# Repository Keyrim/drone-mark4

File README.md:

# drone-mark4 - "throw-drone"

A 5-inch racing drone is thrown by hand, motors off. The firmware detects the
throw, predicts the apex of the parabola, spins the motors up ahead of time,
recovers from an arbitrary attitude (the drone may tumble) and settles into a
stable hover. Everything is rewritten from scratch - firmware, simulator,
tooling - as a deliberate learning project. Behavioral reference: ArduPilot's
"Throw Mode".

Documentation:

- [API reference](https://keyrim.github.io/drone-mark4/) - Doxygen over the C++ of every node plus these pages, published from `main`
- [docs/architecture.md](docs/architecture.md) - system architecture (diagrams)
- [docs/plan-dev.md](docs/plan-dev.md) - development plan and reference document
- [docs/contributing/cpp-guidelines.md](docs/contributing/cpp-guidelines.md) - C++ coding guidelines
- [docs/mobile-app.md](docs/mobile-app.md) - phone as gateway: what the two mobile PoCs established, and the roadmap of `software/mobile`
- [docs/comm-design.md](docs/comm-design.md) - communication stack: transport presence, messaging postman, pull discovery, and the services on the messenger (issues #29 and #31)
- [worktrees/README.md](worktrees/README.md) - git worktrees: where they live, how to bring one up, build it, open it, remove it

## Modules

- `flight-core/` - pure flight core: no dynamic allocation, no
  exceptions/RTTI, no clock access. `float` everywhere
  (`-Wdouble-promotion` as an error).
- `platform/` - 3 abstract services (AbsSensorSource, AbsMotorSink,
  AbsClock) plus one implementation set per variant; commands come in
  through the `messaging` component, not through a platform service. No singletons: each executable has an
  explicit composition root in its main.
- `protocol/` - one protobuf schema (`mark4.proto`), codecs generated at
  build time for C/C++ (nanopb) and GDScript (godobuf); spoken by
  everyone (firmware, sim, Godot, hub).
- `telemetry/` - the registry of named measures a node exposes, declared
  next to the variables they read. A leaf: names, units and pointers, no
  wire. A ground tool discovers the list and streams the subset it wants.
- `transport/` - the interface manager: frames every payload with a source
  and a destination node, learns every node it hears, relays between links.
- `log/` - one logging module per source file, filterable at runtime, its
  lines going out on the wire like everything else.

## Build

### Inside the devcontainer (recommended)

Open `drone-mark4.code-workspace` in VS Code -> "Reopen in Container". The
workspace exposes the repo root and `software/` (the CMake project root) as
folders and carries the debug configurations. Both toolchains (native gcc +
arm-none-eabi) and the pinned tooling live in the image.

```sh
# Desktop: build + tests
cmake --preset desktop && cmake --build --preset desktop && ctest --preset desktop

# Sanitizers (ASan/UBSan)
cmake --preset desktop-san && cmake --build --preset desktop-san && ctest --preset desktop-san

# STM32F405 cross-compilation (Cortex-M4F) -> firmware.elf
cmake --preset stm32 && cmake --build --preset stm32

# Sign of life (runs its loop with or without a plant, no frame limit by default)
./software/build/desktop/drone_sim/drone_sim
```

### Mobile app (Flutter, Android)

`software/mobile/` is the Flutter project; the image carries Flutter, the
Android SDK, the NDK and adb. The phone is reached over Wi-Fi (developer
options -> wireless debugging), the container being on the host network:

```sh
./scripts/adb_wifi.sh                     # discovers the phone over mDNS, pairs once, connects
cd software/mobile && flutter pub get && ./tool/gen.sh   # generated codec, wire hash
flutter run                               # or: flutter build apk --debug --target-platform android-arm64
```

### Manual build (outside the container)

Prerequisites: CMake >= 3.25, Ninja, gcc, arm-none-eabi-gcc (ARM tarball
14.2.rel1), clang-format/clang-tidy 21 for the checks. Same commands as above.

### Code quality

```sh
git ls-files '*.cpp' '*.hpp' '*.c' '*.h' | xargs clang-format --dry-run --Werror
run-clang-tidy -p software/build/desktop "$(pwd)/(apps|flight-core|platform|protocol|tests)/"
```

## Simulation chain

Three processes are transport nodes on udp/47820 and find each other by
the transport's keepalives; the plant and the hub then ask every node that
appears who it is. The Godot plant spawns one virtual drone per node that
answers `drone_sim` and feeds it sensor frames in lockstep, `drone_sim` answers with
actuator frames and streams its status, logs and telemetry to the nodes
that subscribed, the hub decodes it for the pages. Nothing is configured,
start them in any order.

```sh
# Terminal 1 - flight process (one per virtual drone wanted)
./software/build/desktop/drone_sim/drone_sim

# Terminal 2 - the plant (the desktop build generated its codec)
godot --path sim-godot

# Terminal 3 - decoding endpoint and web pages on http://127.0.0.1:47810
./software/build/desktop/hub/hub
```

Every python tool in the repository runs on the standard library alone, so
there is nothing to install first.

## Debugging from VS Code

`drone-mark4.code-workspace` provides:

- `drone_sim (gdb)` - debugs the CMake launch target: pick the `desktop`
  preset and the `drone_sim` target in the CMake Tools status bar, the
  target is rebuilt automatically before each launch;
- `sim_stub (python)` - streams frames until stopped.

The default build task (Ctrl+Shift+B) builds the active CMake configure
preset.

## CI

- `devcontainer-image.yml` - reusable workflow that tags the image by a hash
  of the Dockerfile, builds and pushes it to GHCR
  (`ghcr.io/keyrim/drone-mark4-devcontainer`, public) only when that tag is
  missing, and retags `:latest` on main.
- `ci.yml` and `docs.yml` each call it as a first `image` job and run every
  other job inside the digest it returns, so a Dockerfile change is built and
  tested inside the PR that makes it, with no digest to bump by hand. `ci.yml`
  has 8 parallel jobs: desktop+tests, stm32, esp32, desktop-san, pages,
  mobile (gen, flutter analyze, format, test, debug apk), clang-format+ascii,
  clang-tidy.

## J-Link license note

The development image downloads the J-Link tools from segger.com: the
automated download (`--post-data accept_license_agreement=accepted`) implies
acceptance of the [Segger license](https://www.segger.com/downloads/jlink).
If that is a problem, comment out the J-Link layer in the `Dockerfile` or
install the .deb manually. The whole J-Link stack (`JLinkExe`,
`JLinkGDBServer`, `JLinkRTTClient`) runs inside the container: the probe is
attached to WSL with `usbipd` and reaches the container through the `/dev`
bind mount (see `docs/bring-up.md`).

## License

[MIT](LICENSE).

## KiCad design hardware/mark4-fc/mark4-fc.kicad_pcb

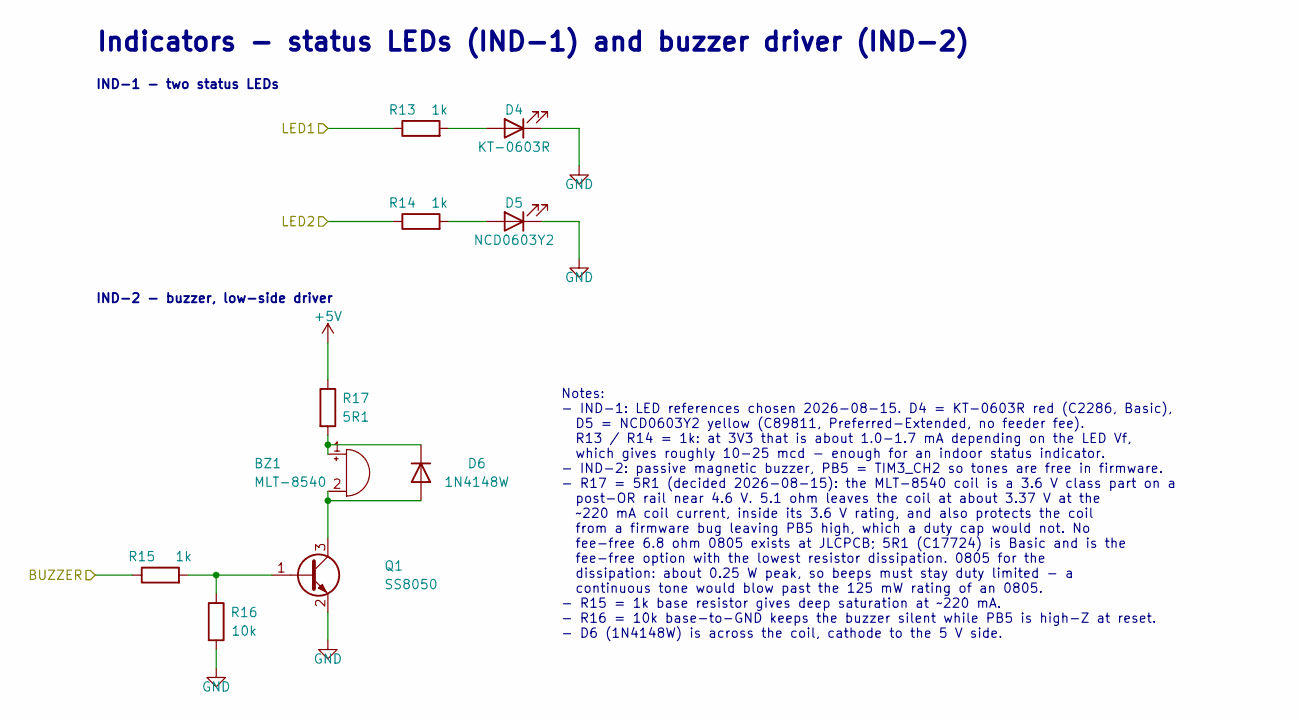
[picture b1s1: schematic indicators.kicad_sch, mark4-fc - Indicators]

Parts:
BZ1: MLT-8540; Buzzer_MLT-8540; MPN MLT-8540; LCSC C95300
D4: KT-0603R; LED_0603_1608Metric; MPN KT-0603R; LCSC C2286
D5: NCD0603Y2; LED_0603_1608Metric; MPN NCD0603Y2; LCSC C89811
D6: 1N4148W; D_SOD-123; MPN 1N4148W; LCSC C81598
Q1: SS8050; SOT-23; MPN S8050; LCSC C2146
R13, R14, R15: 1k; R_0603_1608Metric; MPN 0603WAF1001T5E; LCSC C21190
R16: 10k; R_0603_1608Metric; MPN 0603WAF1002T5E; LCSC C25804
R17: 5R1; R_0805_2012Metric; MPN 0805W8F510KT5E; LCSC C17724

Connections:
+5V: R17.1; also elsewhere on the board
/BUZZER: R15.1; also elsewhere on the board
/LED1: R13.1; also elsewhere on the board
/LED2: R14.1; also elsewhere on the board
GND: D4.1 (K), D5.1 (K), Q1.2 (E), R16.2; also elsewhere on the board
unnamed: BZ1.1 (+), D6.1 (K), R17.2
unnamed: BZ1.2 (-), D6.2 (A), Q1.3 (C)
unnamed: D4.2 (A), R13.2
unnamed: D5.2 (A), R14.2
unnamed: Q1.1 (B), R15.2, R16.1

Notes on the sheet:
IND-2 - buzzer, low-side driver
Notes: - IND-1: LED references chosen 2026-08-15. D4 = KT-0603R red (C2286, Basic), D5 = NCD0603Y2 yellow (C89811, Preferred-Extended, no feeder fee). R13 / R14 = 1k: at 3V3 that is about 1.0-1.7 mA depending on the LED Vf, which gives roughly 10-25 mcd - enough for an indoor status indicator. - IN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
Indicators - status LEDs (IND-1) and buzzer driver (IND-2)
IND-1 - two status LEDs

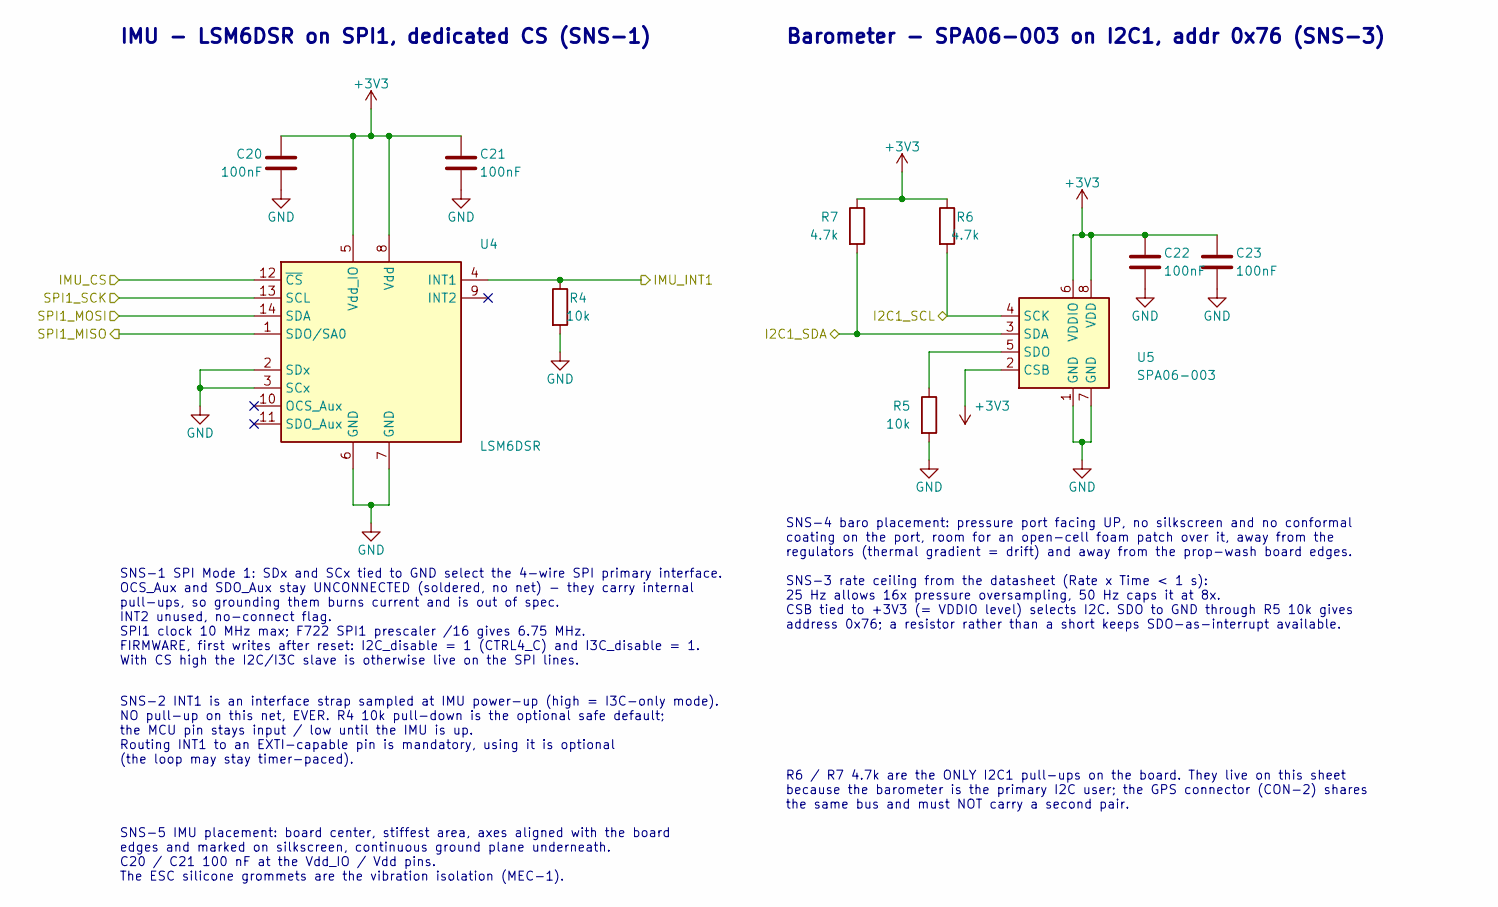
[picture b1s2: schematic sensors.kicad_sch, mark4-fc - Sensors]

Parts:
C20, C21, C22, C23: 100nF; C_0603_1608Metric; MPN CC0603KRX7R9BB104; LCSC C14663
R4, R5: 10k; R_0603_1608Metric; MPN 0603WAF1002T5E; LCSC C25804
R6, R7: 4.7k; R_0603_1608Metric; MPN 0603WAF4701T5E; LCSC C23162
U4: LSM6DSR; LGA-14_3x2.5mm_P0.5mm_LayoutBorder3x4y; MPN LSM6DSRTR; LCSC C784817
U5: SPA06-003; Goertek_LGA-8_2x2.5mm_P0.65mm_ClockwisePinNumbering; MPN SPA06-003; LCSC C30589048

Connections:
+3V3: C20.1, C21.1, C22.1, C23.1, R6.1, R7.1, U4.5 (Vdd_IO), U4.8 (Vdd), U5.2 (CSB), U5.6 (VDDIO), U5.8 (VDD); also elsewhere on the board
/I2C1_SCL: R6.2, U5.4 (SCK); also elsewhere on the board
/I2C1_SDA: R7.2, U5.3 (SDA); also elsewhere on the board
/IMU_CS: U4.12 (~CS); also elsewhere on the board
/IMU_INT1: R4.1, U4.4 (INT1); also elsewhere on the board
/SPI1_MISO: U4.1 (SDO/SA0); also elsewhere on the board
/SPI1_MOSI: U4.14 (SDA); also elsewhere on the board
/SPI1_SCK: U4.13 (SCL); also elsewhere on the board
GND: C20.2, C21.2, C22.2, C23.2, R4.2, R5.2, U4.2 (SDx), U4.3 (SCx), U4.6 (GND), U4.7 (GND), U5.1 (GND), U5.7 (GND); also elsewhere on the board
unnamed: R5.1, U5.5 (SDO)

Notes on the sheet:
SNS-5 IMU placement: board center, stiffest area, axes aligned with the board edges and marked on silkscreen, continuous ground plane underneath. C20 / C21 100 nF at the Vdd_IO / Vdd pins. The ESC silicone grommets are the vibration isolation (MEC-1).
SNS-4 baro placement: pressure port facing UP, no silkscreen and no conformal coating on the port, room for an open-cell foam patch over it, away from the regulators (thermal gradient = drift) and away from the prop-wash board edges. SNS-3 rate ceiling from the datasheet (Rate x Time < 1 s): 25 Hz 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
Barometer - SPA06-003 on I2C1, addr 0x76 (SNS-3)
SNS-1 SPI Mode 1: SDx and SCx tied to GND select the 4-wire SPI primary interface. OCS_Aux and SDO_Aux stay UNCONNECTED (soldered, no net) - they carry internal pull-ups, so grounding them burns current and is out of spec. INT2 unused, no-connect flag. SPI1 clock 10 MHz max; F722 SPI1 prescaler /16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
IMU - LSM6DSR on SPI1, dedicated CS (SNS-1)
SNS-2 INT1 is an interface strap sampled at IMU power-up (high = I3C-only mode). NO pull-up on this net, EVER. R4 10k pull-down is the optional safe default; the MCU pin stays input / low until the IMU is up. Routing INT1 to an EXTI-capable pin is mandatory, using it is optional (the loop may stay 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
R6 / R7 4.7k are the ONLY I2C1 pull-ups on the board. They live on this sheet because the barometer is the primary I2C user; the GPS connector (CON-2) shares the same bus and must NOT carry a second pair.

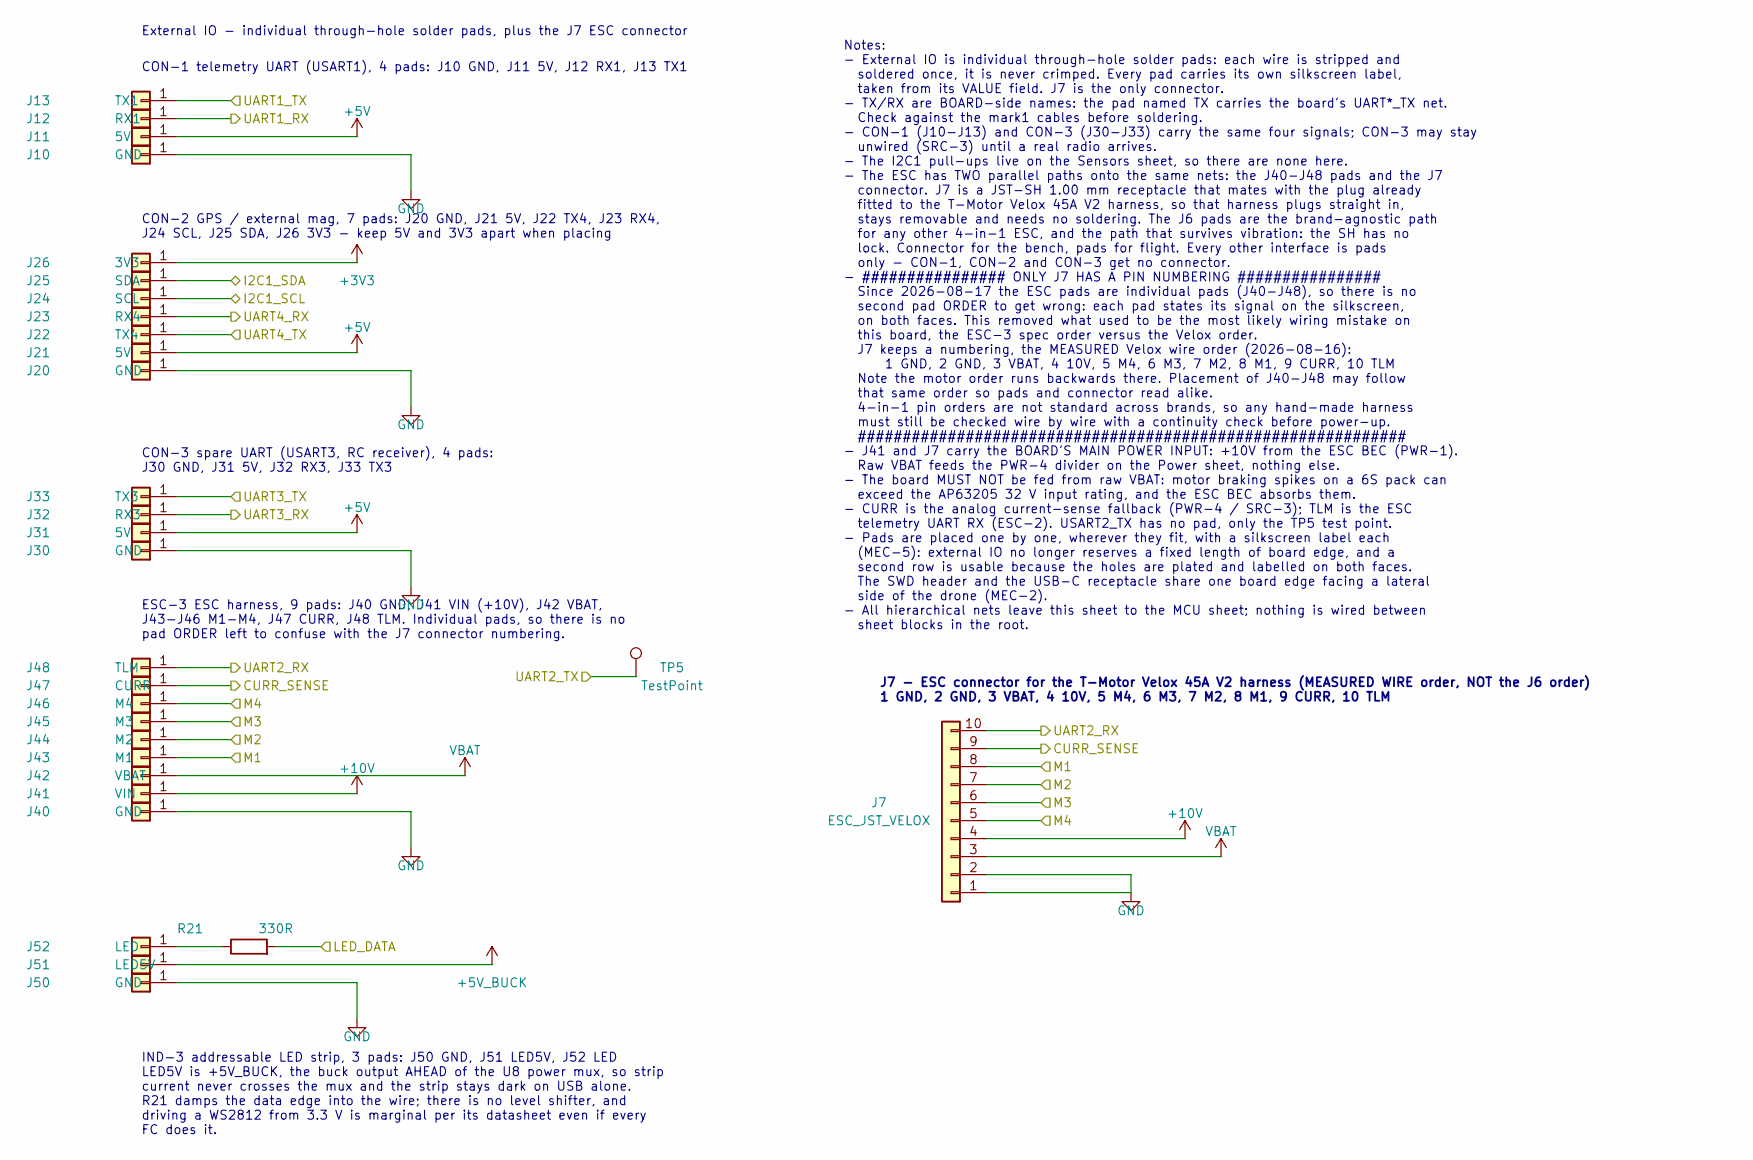
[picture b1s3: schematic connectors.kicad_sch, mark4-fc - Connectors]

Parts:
J7: ESC_JST_VELOX; JST_SH_SM10B-SRSS-TB_1x10-1MP_P1.00mm_Horizontal; MPN SM10B-SRSS-TB(LF)(SN); LCSC C160409
J10, J20, J30, J40, J50: GND; SolderPad_1x01_THT
J11, J21, J31: 5V; SolderPad_1x01_THT
J12: RX1; SolderPad_1x01_THT
J13: TX1; SolderPad_1x01_THT
J22: TX4; SolderPad_1x01_THT
J23: RX4; SolderPad_1x01_THT
J24: SCL; SolderPad_1x01_THT
J25: SDA; SolderPad_1x01_THT
J26: 3V3; SolderPad_1x01_THT
J32: RX3; SolderPad_1x01_THT
J33: TX3; SolderPad_1x01_THT
J41: VIN; SolderPad_1x01_THT
J42: VBAT; SolderPad_1x01_THT
J43: M1; SolderPad_1x01_THT
J44: M2; SolderPad_1x01_THT
J45: M3; SolderPad_1x01_THT
J46: M4; SolderPad_1x01_THT
J47: CURR; SolderPad_1x01_THT
J48: TLM; SolderPad_1x01_THT
J51: LED5V; SolderPad_1x01_THT
J52: LED; SolderPad_1x01_THT
R21: 330R; R_0603_1608Metric; MPN 0603WAF3300T5E; LCSC C23138
TP5: TestPoint; TestPoint_Pad_D1.5mm

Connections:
+3V3: J26.1; also elsewhere on the board
+5V: J11.1, J21.1, J31.1; also elsewhere on the board
+5V_BUCK: J51.1; also elsewhere on the board
+10V: J7.4, J41.1; also elsewhere on the board
/CURR_SENSE: J7.9, J47.1; also elsewhere on the board
/I2C1_SCL: J24.1; also elsewhere on the board
/I2C1_SDA: J25.1; also elsewhere on the board
/LED_DATA: R21.2; also elsewhere on the board
/M1: J7.8, J43.1; also elsewhere on the board
/M2: J7.7, J44.1; also elsewhere on the board
/M3: J7.6, J45.1; also elsewhere on the board
/M4: J7.5, J46.1; also elsewhere on the board
/UART1_RX: J12.1; also elsewhere on the board
/UART1_TX: J13.1; also elsewhere on the board
/UART2_RX: J7.10, J48.1; also elsewhere on the board
/UART2_TX: TP5.1; also elsewhere on the board
/UART3_RX: J32.1; also elsewhere on the board
/UART3_TX: J33.1; also elsewhere on the board
/UART4_RX: J23.1; also elsewhere on the board
/UART4_TX: J22.1; also elsewhere on the board
GND: J7.1, J7.2, J10.1, J20.1, J30.1, J40.1, J50.1; also elsewhere on the board
unnamed: J52.1, R21.1
VBAT: J7.3, J42.1; also elsewhere on the board

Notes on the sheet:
Notes: - External IO is individual through-hole solder pads: each wire is stripped and soldered once, it is never crimped. Every pad carries its own silkscreen label, taken from its VALUE field. J7 is the only connector. - TX/RX are BOARD-side names: the pad named TX carries the board's UART*_TX ne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
J7 - ESC connector for the T-Motor Velox 45A V2 harness (MEASURED WIRE order, NOT the J6 order) 1 GND, 2 GND, 3 VBAT, 4 10V, 5 M4, 6 M3, 7 M2, 8 M1, 9 CURR, 10 TLM
CON-1 telemetry UART (USART1), 4 pads: J10 GND, J11 5V, J12 RX1, J13 TX1
CON-2 GPS / external mag, 7 pads: J20 GND, J21 5V, J22 TX4, J23 RX4, J24 SCL, J25 SDA, J26 3V3 - keep 5V and 3V3 apart when placing
CON-3 spare UART (USART3, RC receiver), 4 pads: J30 GND, J31 5V, J32 RX3, J33 TX3
ESC-3 ESC harness, 9 pads: J40 GND, J41 VIN (+10V), J42 VBAT, J43-J46 M1-M4, J47 CURR, J48 TLM. Individual pads, so there is no pad ORDER left to confuse with the J7 connector numbering.
IND-3 addressable LED strip, 3 pads: J50 GND, J51 LED5V, J52 LED LED5V is +5V_BUCK, the buck output AHEAD of the U8 power mux, so strip current never crosses the mux and the strip stays dark on USB alone. R21 damps the data edge into the wire; there is no level shifter, and driving a WS2812 from 3.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
External IO - individual through-hole solder pads, plus the J7 ESC connector

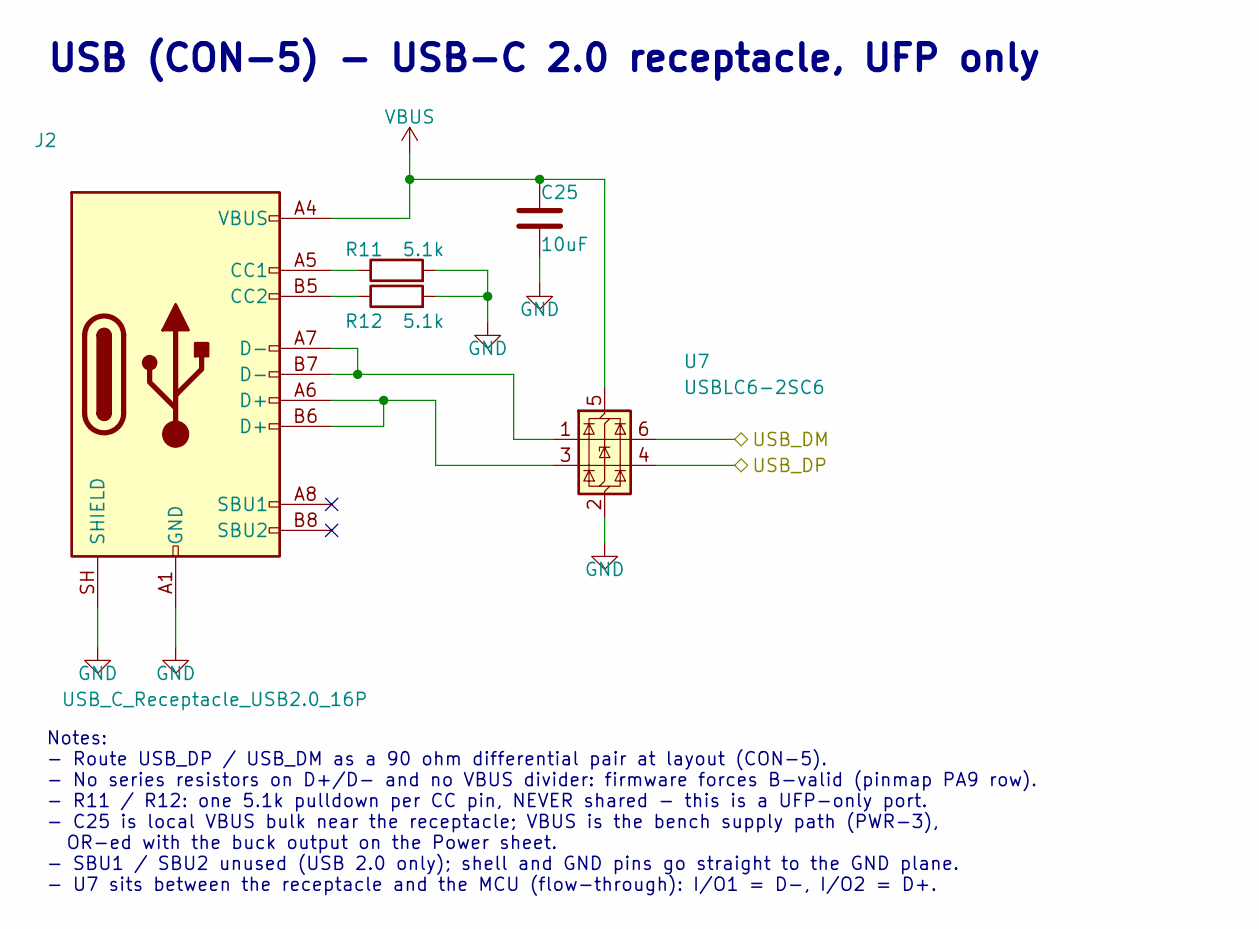
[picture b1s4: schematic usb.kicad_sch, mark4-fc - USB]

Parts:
C25: 10uF; C_0805_2012Metric; MPN CL21A106KAYNNNE; LCSC C15850
J2: USB_C_Receptacle_USB2.0_16P; USB_C_Receptacle_HRO_TYPE-C-31-M-12; MPN TYPE-C-31-M-12; LCSC C165948
R11, R12: 5.1k; R_0603_1608Metric; MPN 0603WAF5101T5E; LCSC C23186
U7: USBLC6-2SC6; SOT-23-6; MPN USBLC6-2SC6; LCSC C7519

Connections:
/USB_DM: U7.6 (I/O1); also elsewhere on the board
/USB_DP: U7.4 (I/O2); also elsewhere on the board
GND: C25.2, J2.A1 (GND), J2.A12 (GND), J2.B1 (GND), J2.B12 (GND), J2.SH (SHIELD), R11.2, R12.2, U7.2 (GND); also elsewhere on the board
unnamed: J2.A5 (CC1), R11.1
unnamed: J2.B5 (CC2), R12.1
unnamed: J2.A6 (D+), J2.B6 (D+), U7.3 (I/O2)
unnamed: J2.A7 (D-), J2.B7 (D-), U7.1 (I/O1)
VBUS: C25.1, J2.A4 (VBUS), J2.A9 (VBUS), J2.B4 (VBUS), J2.B9 (VBUS), U7.5 (VBUS); also elsewhere on the board

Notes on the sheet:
USB (CON-5) - USB-C 2.0 receptacle, UFP only
Notes: - Route USB_DP / USB_DM as a 90 ohm differential pair at layout (CON-5). - No series resistors on D+/D- and no VBUS divider: firmware forces B-valid (pinmap PA9 row). - R11 / R12: one 5.1k pulldown per CC pin, NEVER shared - this is a UFP-only port. - C25 is local VBUS bulk near the receptac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

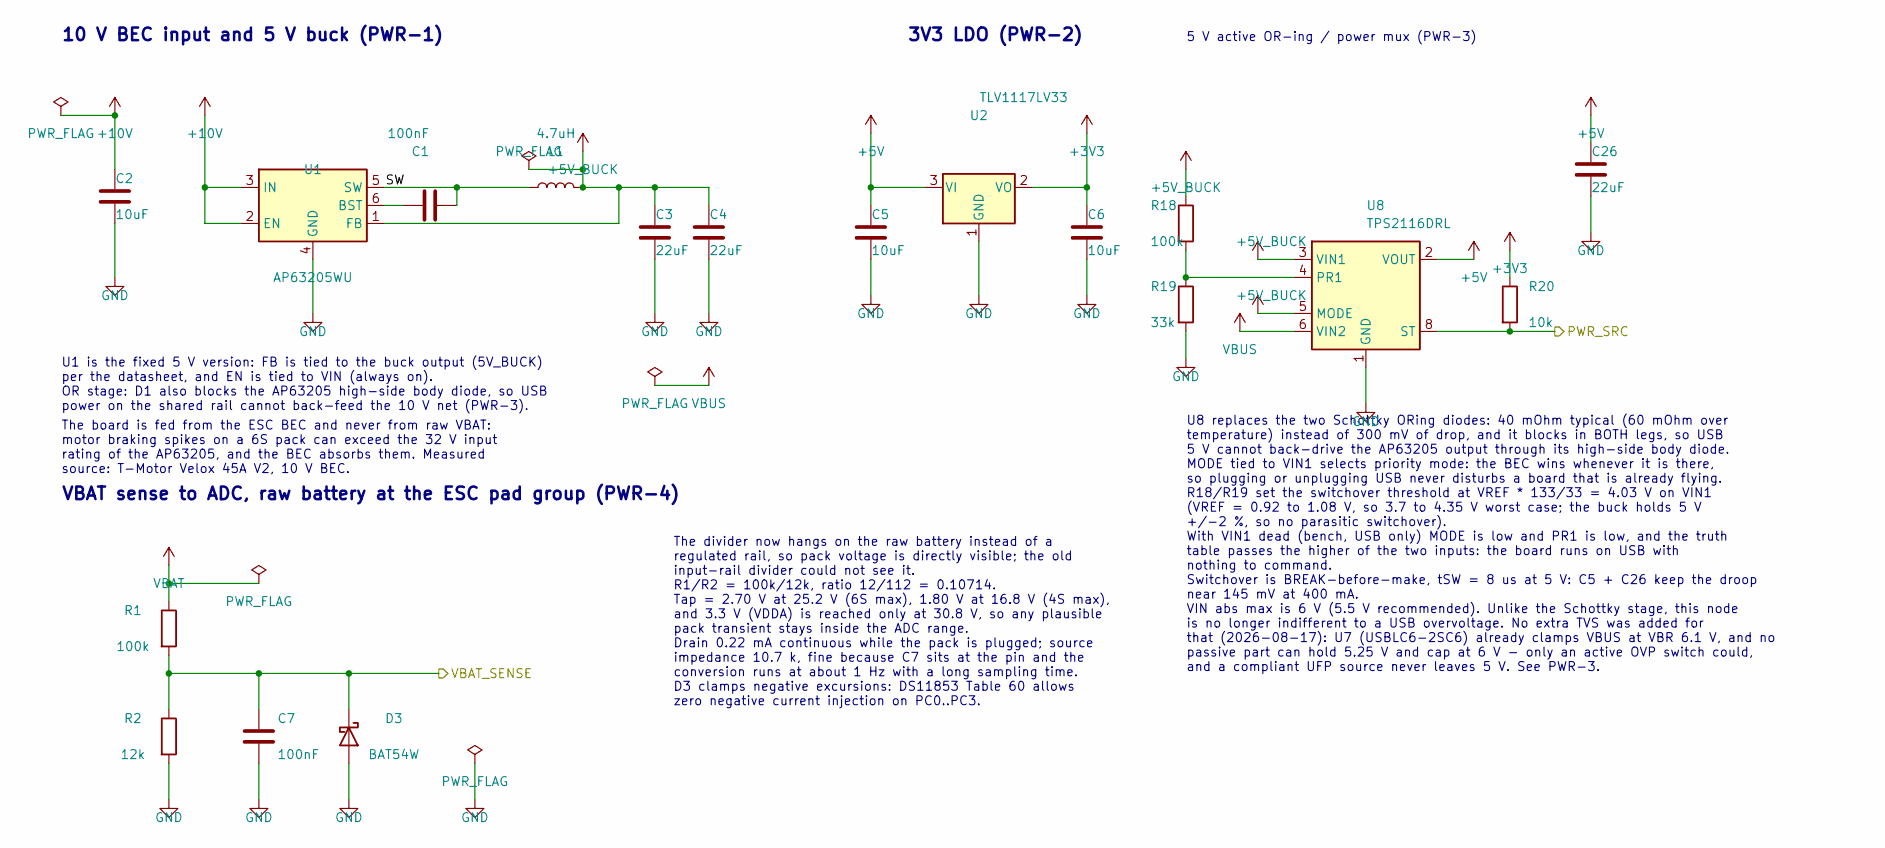
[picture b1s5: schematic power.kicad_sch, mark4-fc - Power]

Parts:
C1, C7: 100nF; C_0603_1608Metric; MPN CC0603KRX7R9BB104; LCSC C14663
C2, C5, C6: 10uF; C_0805_2012Metric; MPN CL21A106KAYNNNE; LCSC C15850
C3, C4, C26: 22uF; C_0805_2012Metric; MPN CL21A226MAQNNNE; LCSC C45783
D3: BAT54W; D_SOD-123; MPN BAT54W; LCSC C7502705
L1: 4.7uH; L_Sunlord_SWPA5040S; MPN SWPA5040S4R7MT; LCSC C48496
R1, R18: 100k; R_0603_1608Metric; MPN 0603WAF1003T5E; LCSC C25803
R2: 12k; R_0603_1608Metric; MPN 0603WAF1202T5E; LCSC C22790
R19: 33k; R_0603_1608Metric; MPN 0603WAF3302T5E; LCSC C4216
R20: 10k; R_0603_1608Metric; MPN 0603WAF1002T5E; LCSC C25804
U1: AP63205WU; TSOT-23-6; MPN AP63205WU-7; LCSC C2071056
U2: TLV1117LV33; SOT-223-3_TabPin2; MPN TLV1117LV33DCYR; LCSC C15578
U8: TPS2116DRL; SOT-583-8; MPN TPS2116DRLR; LCSC C3235557

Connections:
+3V3: C6.1, R20.1, U2.2 (VO); also elsewhere on the board
+5V: C5.1, C26.1, U2.3 (VI), U8.2 (VOUT), U8.7 (VOUT); also elsewhere on the board
+5V_BUCK: C3.1, C4.1, L1.2, R18.1, U1.1 (FB), U8.3 (VIN1), U8.5 (MODE); also elsewhere on the board
+10V: C2.1, U1.2 (EN), U1.3 (IN); also elsewhere on the board
/PWR_SRC: R20.2, U8.8 (ST); also elsewhere on the board
/Power/SW: C1.2, L1.1, U1.5 (SW)
/VBAT_SENSE: C7.1, D3.1 (K), R1.2, R2.1; also elsewhere on the board
GND: C2.2, C3.2, C4.2, C5.2, C6.2, C7.2, C26.2, D3.2 (A), R2.2, R19.2, U1.4 (GND), U2.1 (GND), U8.1 (GND); also elsewhere on the board
unnamed: C1.1, U1.6 (BST)
unnamed: R18.2, R19.1, U8.4 (PR1)
VBAT: R1.1; also elsewhere on the board
VBUS: U8.6 (VIN2); also elsewhere on the board

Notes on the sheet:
The board is fed from the ESC BEC and never from raw VBAT: motor braking spikes on a 6S pack can exceed the 32 V input rating of the AP63205, and the BEC absorbs them. Measured source: T-Motor Velox 45A V2, 10 V BEC.
The divider now hangs on the raw battery instead of a regulated rail, so pack voltage is directly visible; the old input-rail divider could not see it. R1/R2 = 100k/12k, ratio 12/112 = 0.10714. Tap = 2.70 V at 25.2 V (6S max), 1.80 V at 16.8 V (4S max), and 3.3 V (VDDA) is reached only at 30.8 V, s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
3V3 LDO (PWR-2)
VBAT sense to ADC, raw battery at the ESC pad group (PWR-4)
5 V active OR-ing / power mux (PWR-3)
U8 replaces the two Schottky ORing diodes: 40 mOhm typical (60 mOhm over temperature) instead of 300 mV of drop, and it blocks in BOTH legs, so USB 5 V cannot back-drive the AP63205 output through its high-side body diode. MODE tied to VIN1 selects priority mode: the BEC wins whenever it is there, 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
U1 is the fixed 5 V version: FB is tied to the buck output (5V_BUCK) per the datasheet, and EN is tied to VIN (always on). OR stage: D1 also blocks the AP63205 high-side body diode, so USB power on the shared rail cannot back-feed the 10 V net (PWR-3).
10 V BEC input and 5 V buck (PWR-1)

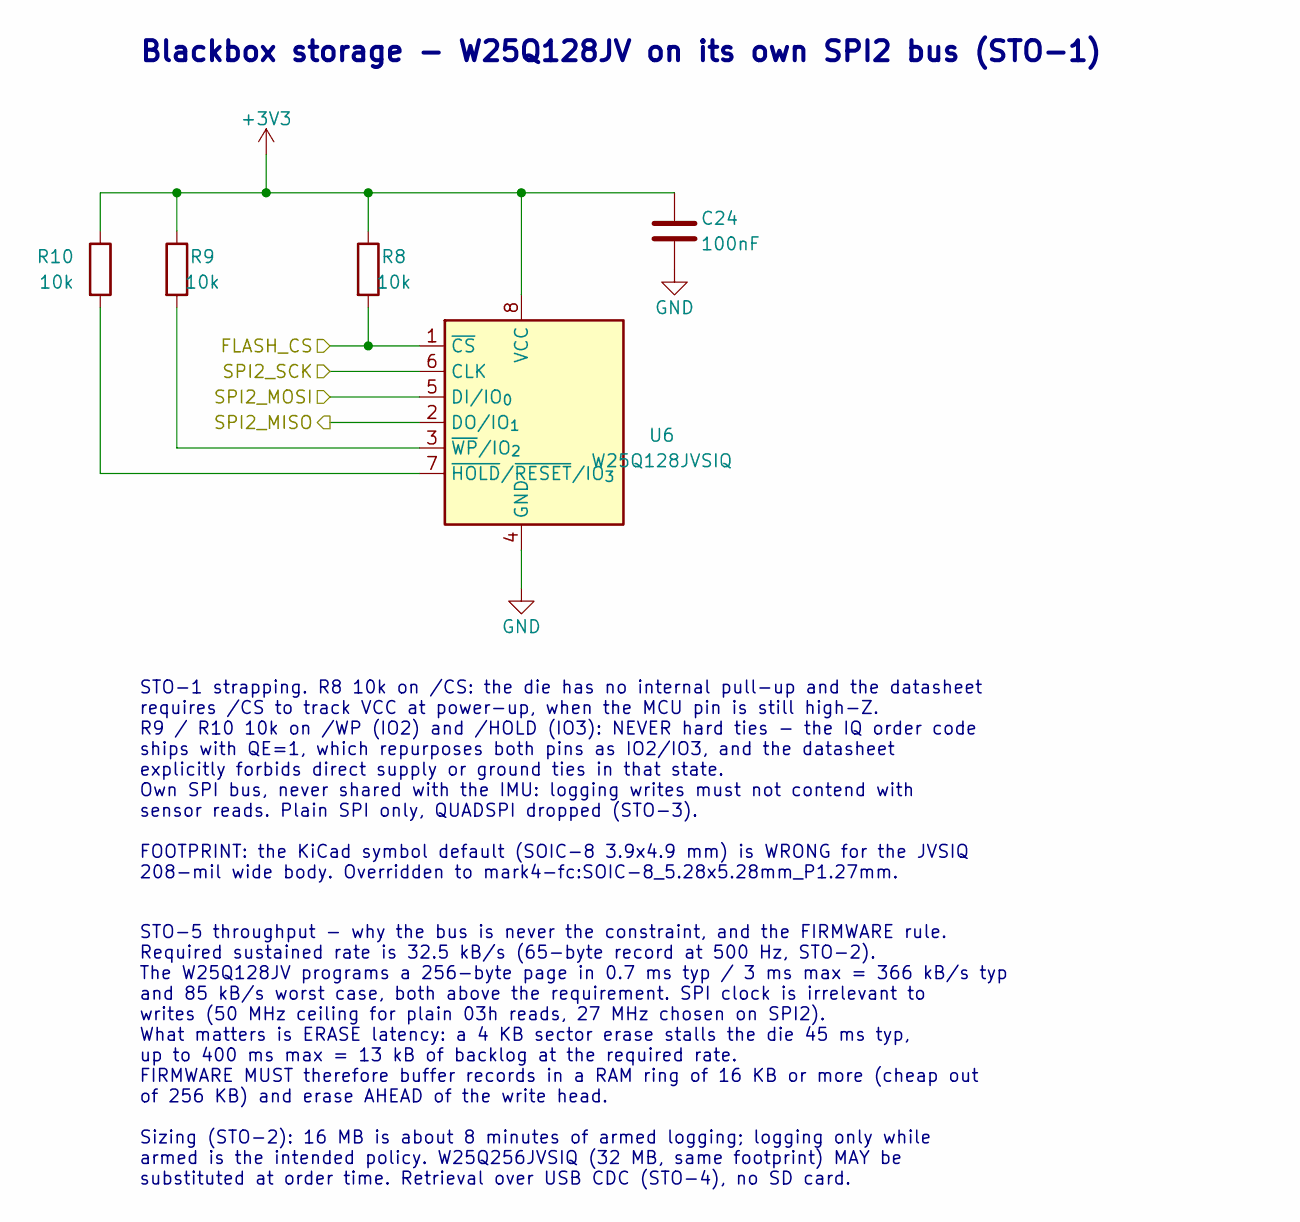
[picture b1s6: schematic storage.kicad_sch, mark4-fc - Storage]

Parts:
C24: 100nF; C_0603_1608Metric; MPN CC0603KRX7R9BB104; LCSC C14663
R8, R9, R10: 10k; R_0603_1608Metric; MPN 0603WAF1002T5E; LCSC C25804
U6: W25Q128JVSIQ; SOIC-8_5.28x5.28mm_P1.27mm; MPN W25Q128JVSIQ; LCSC C97521

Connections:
+3V3: C24.1, R8.1, R9.1, R10.1, U6.8 (VCC); also elsewhere on the board
/FLASH_CS: R8.2, U6.1 (~CS); also elsewhere on the board
/SPI2_MISO: U6.2 (DO/IO_{1}); also elsewhere on the board
/SPI2_MOSI: U6.5 (DI/IO_{0}); also elsewhere on the board
/SPI2_SCK: U6.6 (CLK); also elsewhere on the board
GND: C24.2, U6.4 (GND); also elsewhere on the board
unnamed: R10.2, U6.7 (~HOLD/~RESET/IO_{3})
unnamed: R9.2, U6.3 (~WP/IO_{2})

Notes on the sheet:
Blackbox storage - W25Q128JV on its own SPI2 bus (STO-1)
STO-1 strapping. R8 10k on /CS: the die has no internal pull-up and the datasheet requires /CS to track VCC at power-up, when the MCU pin is still high-Z. R9 / R10 10k on /WP (IO2) and /HOLD (IO3): NEVER hard ties - the IQ order code ships with QE=1, which repurposes both pins as IO2/IO3, and the d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
STO-5 throughput - why the bus is never the constraint, and the FIRMWARE rule. Required sustained rate is 32.5 kB/s (65-byte record at 500 Hz, STO-2). The W25Q128JV programs a 256-byte page in 0.7 ms typ / 3 ms max = 366 kB/s typ and 85 kB/s worst case, both above the requirement. SPI clock is irre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

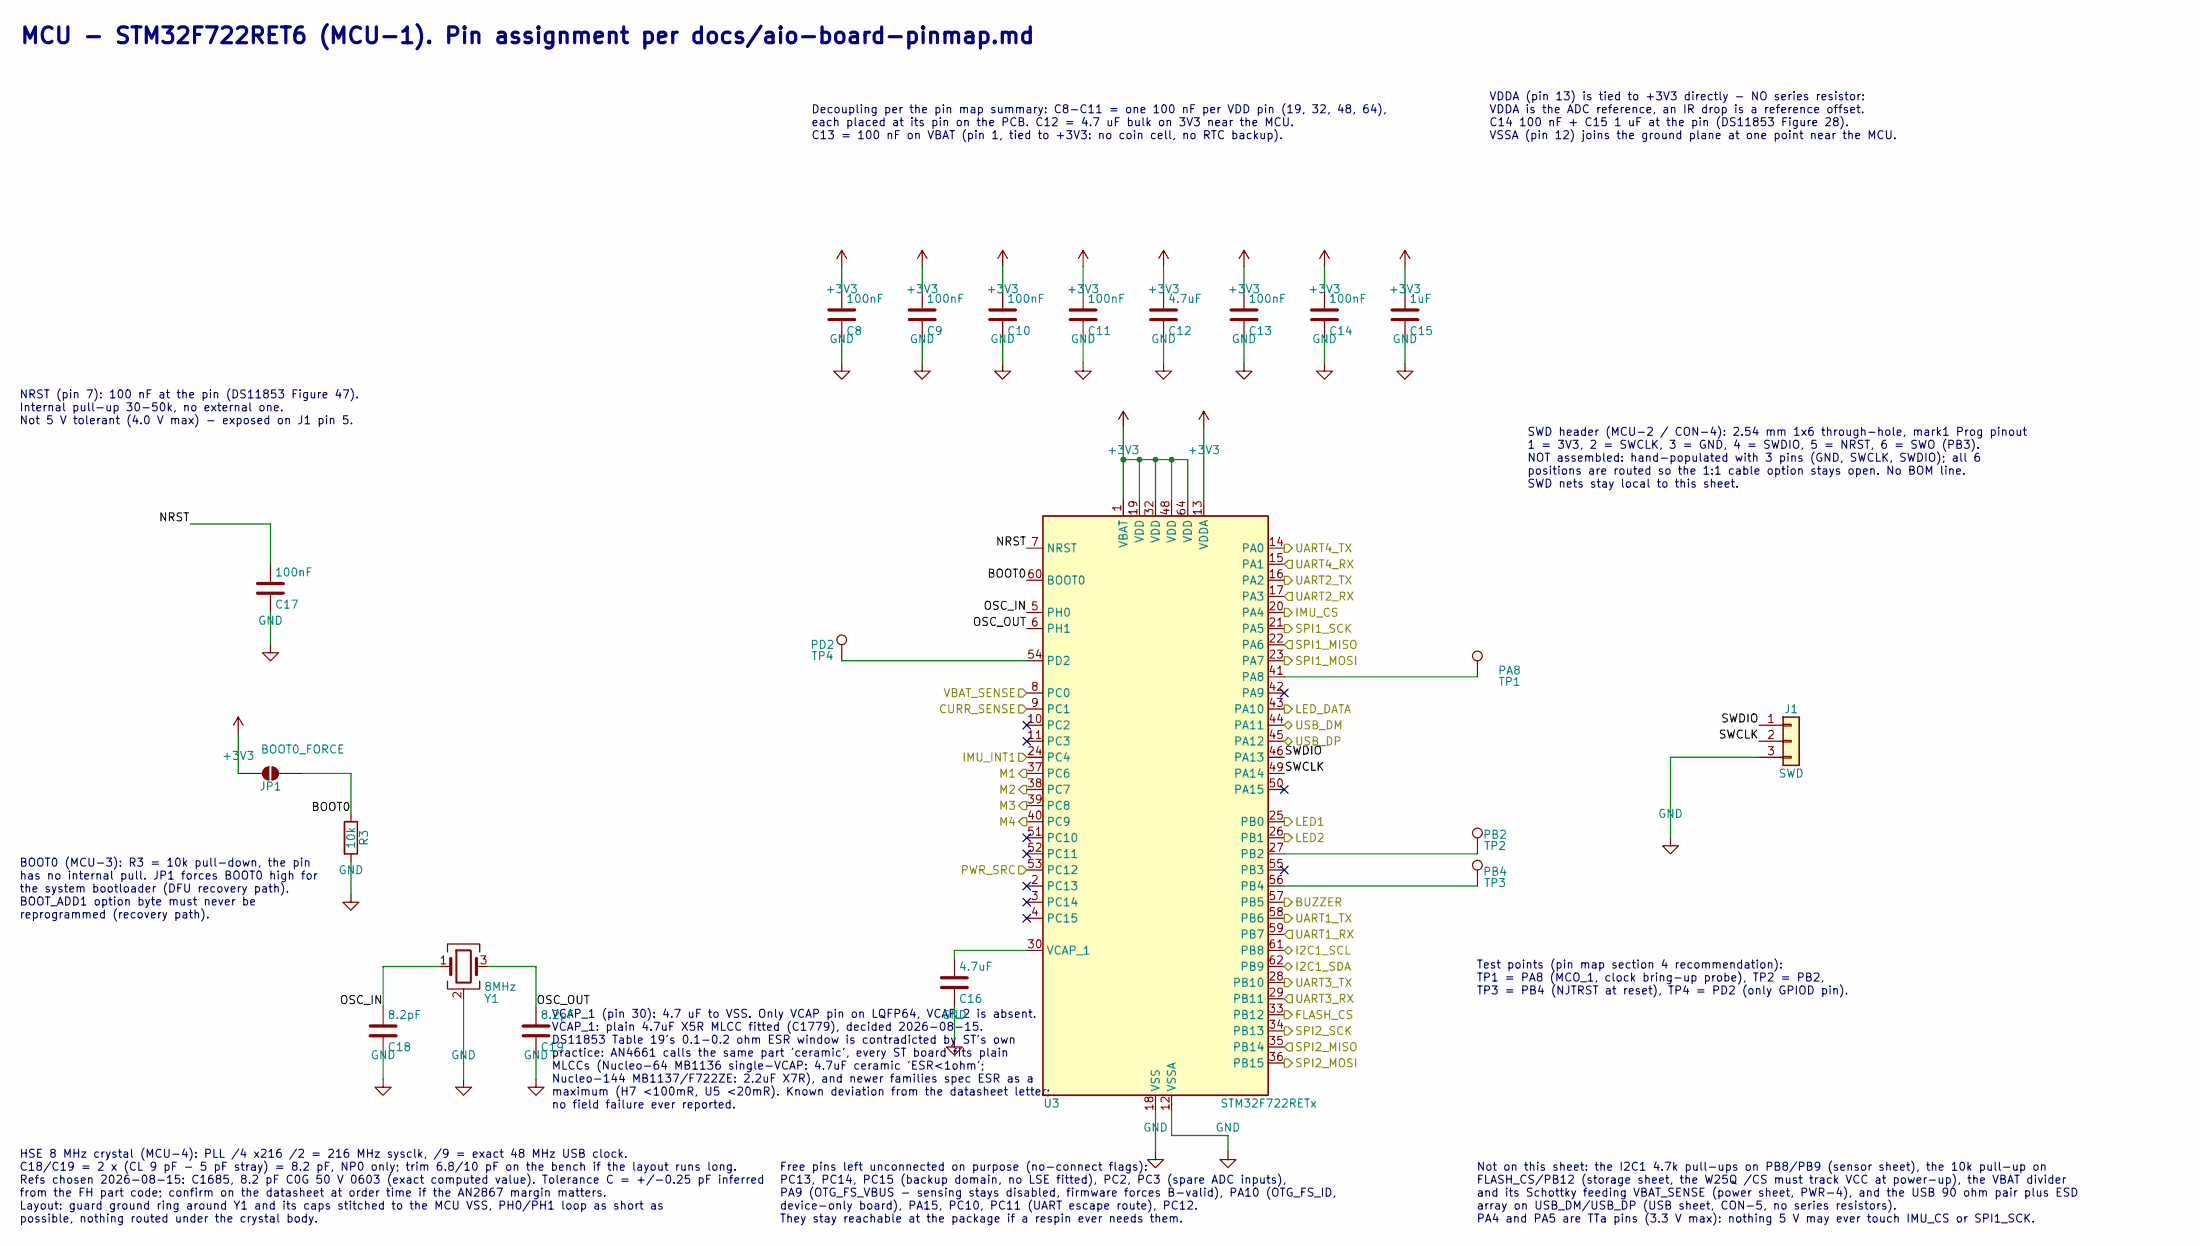
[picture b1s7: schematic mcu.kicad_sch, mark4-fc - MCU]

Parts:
C8, C9, C10, C11, C13, C14, C17: 100nF; C_0603_1608Metric; MPN CC0603KRX7R9BB104; LCSC C14663
C12, C16: 4.7uF; C_0805_2012Metric; MPN CL21A475KAQNNNE; LCSC C1779
C15: 1uF; C_0603_1608Metric; MPN CL10A105KB8NNNC; LCSC C15849
C18, C19: 8.2pF; C_0603_1608Metric; MPN 0603CG8R2C500NT; LCSC C1685
J1: SWD; PinHeader_1x03_P2.54mm_Vertical
JP1: BOOT0_FORCE; SolderJumper-2_P1.3mm_Open_TrianglePad1.0x1.5mm
R3: 10k; R_0603_1608Metric; MPN 0603WAF1002T5E; LCSC C25804
TP1: PA8; TestPoint_Pad_D1.5mm
TP2: PB2; TestPoint_Pad_D1.5mm
TP3: PB4; TestPoint_Pad_D1.5mm
TP4: PD2; TestPoint_Pad_D1.5mm
U3: STM32F722RETx; LQFP-64_10x10mm_P0.5mm; MPN STM32F722RET6; LCSC C118207
Y1: 8MHz; Crystal_SMD_3225-4Pin_3.2x2.5mm; MPN CJ13-080000910B20; LCSC C712812

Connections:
+3V3: C8.1, C9.1, C10.1, C11.1, C12.1, C13.1, C14.1, C15.1, JP1.1 (A), U3.1 (VBAT), U3.13 (VDDA), U3.19 (VDD), U3.32 (VDD), U3.48 (VDD), U3.64 (VDD); also elsewhere on the board
/BUZZER: U3.57 (PB5); also elsewhere on the board
/CURR_SENSE: U3.9 (PC1); also elsewhere on the board
/FLASH_CS: U3.33 (PB12); also elsewhere on the board
/I2C1_SCL: U3.61 (PB8); also elsewhere on the board
/I2C1_SDA: U3.62 (PB9); also elsewhere on the board
/IMU_CS: U3.20 (PA4); also elsewhere on the board
/IMU_INT1: U3.24 (PC4); also elsewhere on the board
/LED1: U3.25 (PB0); also elsewhere on the board
/LED2: U3.26 (PB1); also elsewhere on the board
/LED_DATA: U3.43 (PA10); also elsewhere on the board
/M1: U3.37 (PC6); also elsewhere on the board
/M2: U3.38 (PC7); also elsewhere on the board
/M3: U3.39 (PC8); also elsewhere on the board
/M4: U3.40 (PC9); also elsewhere on the board
/MCU/BOOT0: JP1.2 (B), R3.1, U3.60 (BOOT0)
/MCU/NRST: C17.1, U3.7 (NRST)
/MCU/OSC_IN: C18.1, U3.5 (PH0), Y1.1
/MCU/OSC_OUT: C19.1, U3.6 (PH1), Y1.3
/MCU/SWCLK: J1.2, U3.49 (PA14)
/MCU/SWDIO: J1.1, U3.46 (PA13)
/MCU/SWO: U3.55 (PB3)
/PWR_SRC: U3.53 (PC12); also elsewhere on the board
/SPI1_MISO: U3.22 (PA6); also elsewhere on the board
/SPI1_MOSI: U3.23 (PA7); also elsewhere on the board
/SPI1_SCK: U3.21 (PA5); also elsewhere on the board
/SPI2_MISO: U3.35 (PB14); also elsewhere on the board
/SPI2_MOSI: U3.36 (PB15); also elsewhere on the board
/SPI2_SCK: U3.34 (PB13); also elsewhere on the board
/UART1_RX: U3.59 (PB7); also elsewhere on the board
/UART1_TX: U3.58 (PB6); also elsewhere on the board
/UART2_RX: U3.17 (PA3); also elsewhere on the board
/UART2_TX: U3.16 (PA2); also elsewhere on the board
/UART3_RX: U3.29 (PB11); also elsewhere on the board
/UART3_TX: U3.28 (PB10); also elsewhere on the board
/UART4_RX: U3.15 (PA1); also elsewhere on the board
/UART4_TX: U3.14 (PA0); also elsewhere on the board
/USB_DM: U3.44 (PA11); also elsewhere on the board
/USB_DP: U3.45 (PA12); also elsewhere on the board
/VBAT_SENSE: U3.8 (PC0); also elsewhere on the board
GND: C8.2, C9.2, C10.2, C11.2, C12.2, C13.2, C14.2, C15.2, C16.2, C17.2, C18.2, C19.2, J1.3, R3.2, U3.12 (VSSA), U3.18 (VSS), U3.31 (VSS), U3.47 (VSS), U3.63 (VSS), Y1.2 (G), Y1.4 (G); also elsewhere on the board
unnamed: TP1.1, U3.41 (PA8)
unnamed: TP2.1, U3.27 (PB2)
unnamed: TP3.1, U3.56 (PB4)
unnamed: TP4.1, U3.54 (PD2)
unnamed: C16.1, U3.30 (VCAP_1)

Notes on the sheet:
Test points (pin map section 4 recommendation): TP1 = PA8 (MCO_1, clock bring-up probe), TP2 = PB2, TP3 = PB4 (NJTRST at reset), TP4 = PD2 (only GPIOD pin).
HSE 8 MHz crystal (MCU-4): PLL /4 x216 /2 = 216 MHz sysclk, /9 = exact 48 MHz USB clock. C18/C19 = 2 x (CL 9 pF - 5 pF stray) = 8.2 pF, NP0 only; trim 6.8/10 pF on the bench if the layout runs long. Refs chosen 2026-08-15: C1685, 8.2 pF C0G 50 V 0603 (exact computed value). Tolerance C = +/-0.25 pF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
SWD header (MCU-2 / CON-4): 2.54 mm 1x6 through-hole, mark1 Prog pinout 1 = 3V3, 2 = SWCLK, 3 = GND, 4 = SWDIO, 5 = NRST, 6 = SWO (PB3). NOT assembled: hand-populated with 3 pins (GND, SWCLK, SWDIO); all 6 positions are routed so the 1:1 cable option stays open. No BOM line. SWD nets stay local to 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
BOOT0 (MCU-3): R3 = 10k pull-down, the pin has no internal pull. JP1 forces BOOT0 high for the system bootloader (DFU recovery path). BOOT_ADD1 option byte must never be reprogrammed (recovery path).
Not on this sheet: the I2C1 4.7k pull-ups on PB8/PB9 (sensor sheet), the 10k pull-up on FLASH_CS/PB12 (storage sheet, the W25Q /CS must track VCC at power-up), the VBAT divider and its Schottky feeding VBAT_SENSE (power sheet, PWR-4), and the USB 90 ohm pair plus ESD array on USB_DM/USB_DP (USB she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
Free pins left unconnected on purpose (no-connect flags): PC13, PC14, PC15 (backup domain, no LSE fitted), PC2, PC3 (spare ADC inputs), PA9 (OTG_FS_VBUS - sensing stays disabled, firmware forces B-valid), PA10 (OTG_FS_ID, device-only board), PA15, PC10, PC11 (UART escape route), PC12. They stay rea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
VDDA (pin 13) is tied to +3V3 directly - NO series resistor: VDDA is the ADC reference, an IR drop is a reference offset. C14 100 nF + C15 1 uF at the pin (DS11853 Figure 28). VSSA (pin 12) joins the ground plane at one point near the MCU.
MCU - STM32F722RET6 (MCU-1). Pin assignment per docs/aio-board-pinmap.md
Decoupling per the pin map summary: C8-C11 = one 100 nF per VDD pin (19, 32, 48, 64), each placed at its pin on the PCB. C12 = 4.7 uF bulk on 3V3 near the MCU. C13 = 100 nF on VBAT (pin 1, tied to +3V3: no coin cell, no RTC backup).
VCAP_1 (pin 30): 4.7 uF to VSS. Only VCAP pin on LQFP64, VCAP_2 is absent. VCAP_1: plain 4.7uF X5R MLCC fitted (C1779), decided 2026-08-15. DS11853 Table 19's 0.1-0.2 ohm ESR window is contradicted by ST's own practice: AN4661 calls the same part 'ceramic', every ST board fits plain MLCCs (Nucleo-6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
NRST (pin 7): 100 nF at the pin (DS11853 Figure 47). Internal pull-up 30-50k, no external one. Not 5 V tolerant (4.0 V max) - exposed on J1 pin 5.
